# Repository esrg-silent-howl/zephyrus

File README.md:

# Zephyrus
## Hand Motion-Controlled Remote Car

### Problem Statement
Recent developments in research of motion-tracking and gesture-controlled robotic
products have shone a new light on entertainment, special needs teaching, and
accessibility-focused applications. Products like motion-sensing console controllers,
robotic arms, and prosthetics have popularized and extended the knowledge on gesture
and impulse-based technologies throughout the past few years, and their market
is predicted to continue to grow in the future.
To provide a better understanding of the concepts associated with the forementioned
technologies through Research and Development (R&D), the project will consist of a
gesture-controlled car with a wristband as a remote controller. The user will be able to
accelerate and steer the vehicle using natural wrist and finger movements.

Team:
- Hugo Carvalho @HugoDaniel99
- José Mendes @h0wl-14

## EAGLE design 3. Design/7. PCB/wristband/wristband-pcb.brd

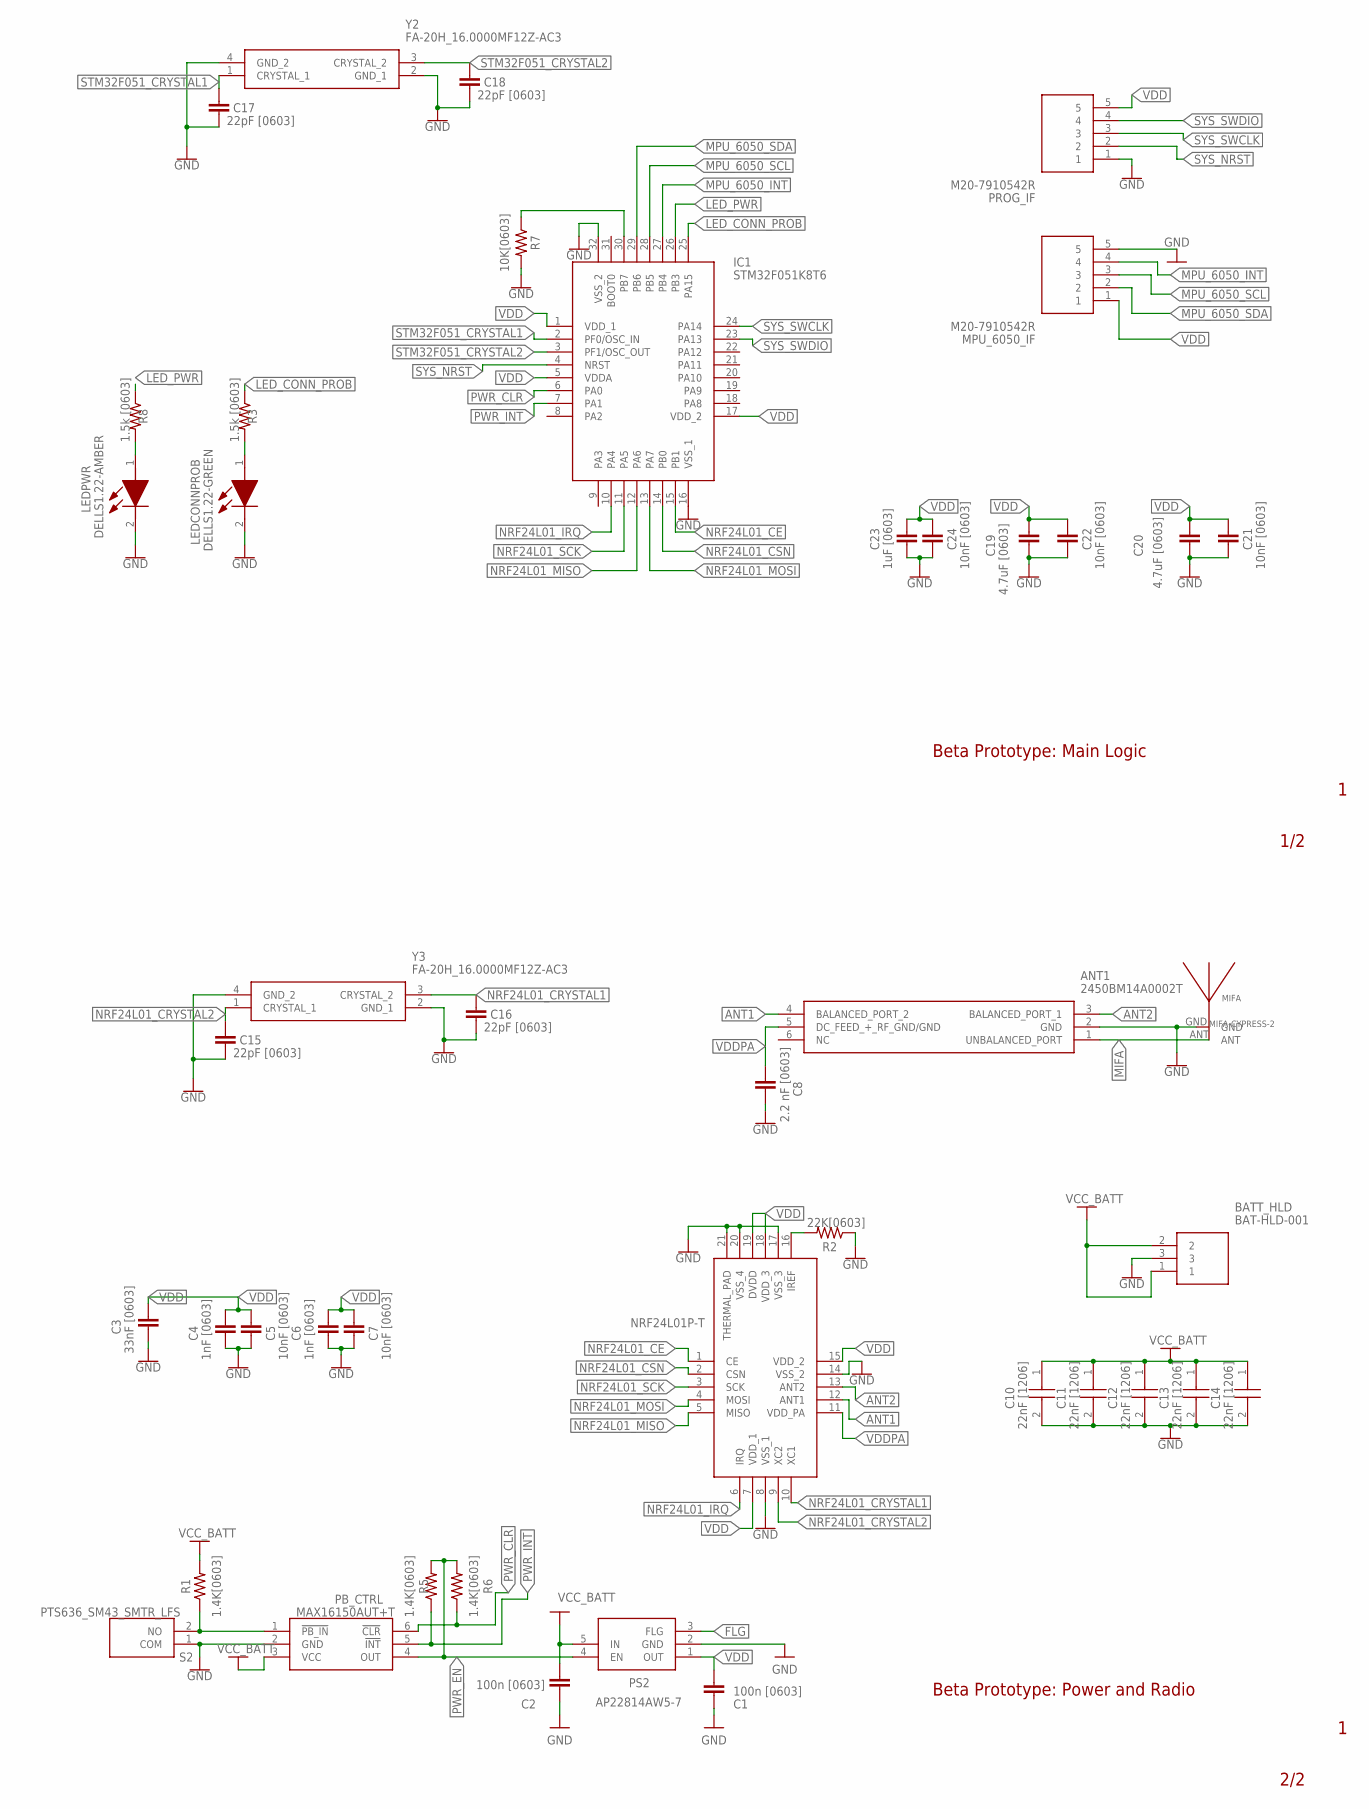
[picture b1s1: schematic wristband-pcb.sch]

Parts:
ANT1: 2450BM14A0002T
BATT_HLD: BAT-HLD-001; BATHLD001
C1, C2: 100n [0603]; CAPC1608X85
C3: 33nF [0603]; RESC0603_L
C4, C6: 1nF [0603]; RESC0603_L
C5, C7, C21, C22, C24: 10nF [0603]; RESC0603_L
C8: 2.2 nF [0603]; RESC0603_L
C10, C11, C12, C13, C14: 22nF [1206]; CAPC3216X180N
C15, C16, C17, C18: 22pF [0603]; RESC0603_L
C19, C20: 4.7uF [0603]; RESC0603_L
C23: 1uF [0603]; RESC0603_L
IC1: STM32F051K8T6; QFP80P900X900X160-32N
LEDCONNPROB: DELLS1.22-GREEN; KSDELLS122JHKI1
LEDPWR: DELLS1.22-AMBER; KSDELLS122JHKI1
MIFA: MIFA-CYPRESS-2
MPU_6050_IF: M20-7910542R; M207910542R
NRF24L01+: NRF24L01P-T; QFN50P400X400X95-21N
PB_CTRL: MAX16150AUT+T; SOT95P280X145-6N
PROG_IF: M20-7910542R; M207910542R
PS2: AP22814AW5-7; SOT95P285X130-5N
R1, R5, R6: 1.4K[0603]; RESC1608X60
R2: 22K[0603]; RESC1608X60
R3, R8: 1.5k [0603]; RESC1608X60
R7: 10K[0603]; RESC1608X60
S2: PTS636_SM43_SMTR_LFS; PTS636SM43SMTRLFS
Y2, Y3: FA-20H_16.0000MF12Z-AC3; FA20H160000MF12ZAC3

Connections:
ANT1: ANT1.4 (BALANCED_PORT_2), NRF24L01+.12 (ANT1)
ANT2: ANT1.3 (BALANCED_PORT_1), NRF24L01+.13 (ANT2)
FLG: PS2.3 (FLG)
GND: ANT1.2 (GND), BATT_HLD.3, C1.2, C2.2, C3.2, C4.2, C5.2, C6.2, C7.2, C8.2, C10.2, C11.2, C12.2, C13.2, C14.2, C15.2, C16.2, C17.2, C18.2, C19.2, C20.2, C21.2, C22.2, C23.2, C24.2, IC1.16 (VSS_1), IC1.32 (VSS_2), LEDCONNPROB.2 (K), LEDPWR.2 (K), MIFA.GND, MPU_6050_IF.5, NRF24L01+.8 (VSS_1), NRF24L01+.14 (VSS_2), NRF24L01+.17 (VSS_3), NRF24L01+.20 (VSS_4), NRF24L01+.21 (THERMAL_PAD), PB_CTRL.2 (GND), PROG_IF.1, PS2.2 (GND), R2.1, R7.2, S2.1 (COM), Y2.2 (GND_1), Y2.4 (GND_2), Y3.2 (GND_1), Y3.4 (GND_2)
LED_CONN_PROB: IC1.25 (PA15), R3.1
LED_PWR: IC1.26 (PB3), R8.1
MIFA: ANT1.1 (UNBALANCED_PORT), MIFA.ANT
MPU_6050_INT: IC1.27 (PB4), MPU_6050_IF.4
MPU_6050_SCL: IC1.28 (PB5), MPU_6050_IF.3
MPU_6050_SDA: IC1.29 (PB6), MPU_6050_IF.2
unnamed: PB_CTRL.1 (!PB_IN), R1.1, S2.2 (NO)
unnamed: NRF24L01+.16 (IREF), R2.2
unnamed: IC1.30 (PB7), R7.1
unnamed: LEDPWR.1 (A), R8.2
unnamed: LEDCONNPROB.1 (A), R3.2
NRF24L01_CE: IC1.15 (PB1), NRF24L01+.1 (CE)
NRF24L01_CRYSTAL1: C16.1, NRF24L01+.10 (XC1), Y3.3 (CRYSTAL_2)
NRF24L01_CRYSTAL2: C15.1, NRF24L01+.9 (XC2), Y3.1 (CRYSTAL_1)
NRF24L01_CSN: IC1.14 (PB0), NRF24L01+.2 (CSN)
NRF24L01_IRQ: IC1.10 (PA4), NRF24L01+.6 (IRQ)
NRF24L01_MISO: IC1.12 (PA6), NRF24L01+.5 (MISO)
NRF24L01_MOSI: IC1.13 (PA7), NRF24L01+.4 (MOSI)
NRF24L01_SCK: IC1.11 (PA5), NRF24L01+.3 (SCK)
PWR_CLR: IC1.6 (PA0), PB_CTRL.6 (!CLR), R6.1
PWR_EN: PB_CTRL.4 (OUT), PS2.4 (EN), R5.2, R6.2
PWR_INT: IC1.7 (PA1), PB_CTRL.5 (!INT), R5.1
STM32F051_CRYSTAL1: C17.1, IC1.2 (PF0/OSC_IN), Y2.1 (CRYSTAL_1)
STM32F051_CRYSTAL2: C18.1, IC1.3 (PF1/OSC_OUT), Y2.3 (CRYSTAL_2)
SYS_NRST: IC1.4 (NRST), PROG_IF.2
SYS_SWCLK: IC1.24 (PA14), PROG_IF.3
SYS_SWDIO: IC1.23 (PA13), PROG_IF.4
VCC_BATT: BATT_HLD.1, BATT_HLD.2, C2.1, C10.1, C11.1, C12.1, C13.1, C14.1, PB_CTRL.3 (VCC), PS2.5 (IN), R1.2
VDD: C1.1, C3.1, C4.1, C5.1, C6.1, C7.1, C19.1, C20.1, C21.1, C22.1, C23.1, C24.1, IC1.1 (VDD_1), IC1.5 (VDDA), IC1.17 (VDD_2), MPU_6050_IF.1, NRF24L01+.7 (VDD_1), NRF24L01+.15 (VDD_2), NRF24L01+.18 (VDD_3), NRF24L01+.19 (DVDD), PROG_IF.5, PS2.1 (OUT)
VDDPA: ANT1.5 (DC_FEED_+_RF_GND/GND), C8.1, NRF24L01+.11 (VDD_PA)

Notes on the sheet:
1/2
2/2
Beta Prototype: Main Logic
Beta Prototype: Power and Radio

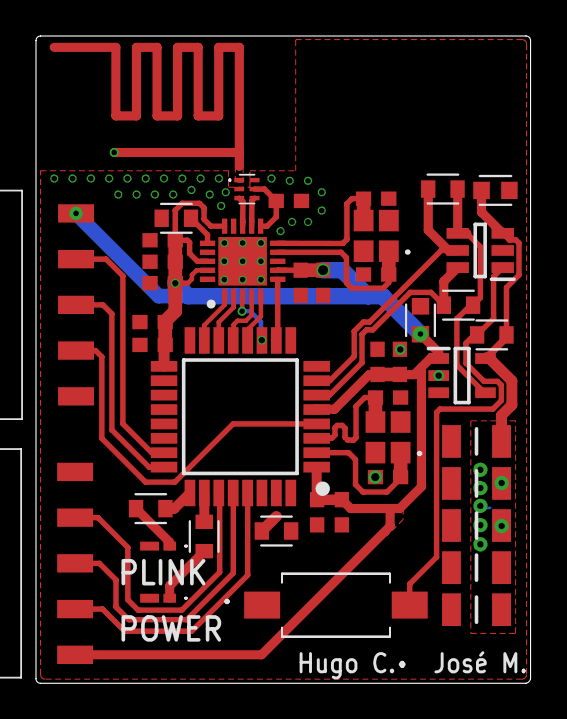
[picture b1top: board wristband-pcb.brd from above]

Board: 2 copper layers, 27.5 x 36.0 mm, 44 parts (1 on the bottom side), 33 nets.

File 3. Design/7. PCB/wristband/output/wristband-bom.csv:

Qty,Value,Device,Package,Parts,Description,Column1,_1
3,1.4K[0603],R-US_CHIP-0603(1608-METRIC),RESC1608X60,"R1, R5, R6",Resistor Fixed - ANSI,,
2,1.5k [0603],R-US_CHIP-0603(1608-METRIC),RESC1608X60,"R3, R8",Resistor Fixed - ANSI,,
2,100n [0603],C_CHIP-0603(1608-METRIC),CAPC1608X85,"C1, C2",Capacitor - Generic,,
1,10K[0603],R-US_CHIP-0603(1608-METRIC),RESC1608X60,R7,Resistor Fixed - ANSI,,
5,10nF [0603],CAPACITOR_0603_L,RESC0603_L,"C5, C7, C21, C22, C24",Generic chip capacitor,,
2,1nF [0603],CAPACITOR_0603_L,RESC0603_L,"C4, C6",Generic chip capacitor,,
1,1uF [0603],CAPACITOR_0603_L,RESC0603_L,C23,Generic chip capacitor,,
1,2.2 nF [0603],CAPACITOR_0603_L,RESC0603_L,C8,Generic chip capacitor,,
1,22K[0603],R-US_CHIP-0603(1608-METRIC),RESC1608X60,R2,Resistor Fixed - ANSI,,
5,22nF [1206],CL31B226KPHNNNE,CAPC3216X180N,"C10, C11, C12, C13, C14",22F +/-10% 10V Ceramic Capacitor X7R 1206 (3216 Metric),,
4,22pF [0603],CAPACITOR_0603_L,RESC0603_L,"C15, C16, C17, C18",Generic chip capacitor,,
1,2450BM14A0002T,2450BM14A0002T,2450BM14A0002T,ANT1,"JOHANSON TECHNOLOGY - 2450BM14A0002T - BALUN, 2.45GHZ, IMPEDANCE MATCHED",,
1,33nF [0603],CAPACITOR_0603_L,RESC0603_L,C3,Generic chip capacitor,,
2,4.7uF [0603],CAPACITOR_0603_L,RESC0603_L,"C19, C20",Generic chip capacitor,,
1,AP22814AW5-7,AP22814AW5-7,SOT95P285X130-5N,PS2,"DiodesZetex AP22814AW5-7, USB Power Switch, High Side, 65m, 1.6 V min. 5-Pin, SOT25",,
1,BAT-HLD-001,BAT-HLD-001,BATHLD001,BATT_HLD,Coin Cell Battery Holders Linx CR2032 Battery Holder,,
1,DELLS1.22-AMBER,KS_DELLS1.22-JHKI-1,KSDELLS122JHKI1,LEDPWR,Standard LEDs - SMD Super Red TOPLED E 1608,,
1,DELLS1.22-GREEN,KS_DELLS1.22-JHKI-1,KSDELLS122JHKI1,LEDCONNPROB,Standard LEDs - SMD Super Red TOPLED E 1608,,
2,FA-20H_16.0000MF12Z-AC3,FA-20H_16.0000MF12Z-AC3,FA20H160000MF12ZAC3,"Y2, Y3",Crystals 16MHz 10ppm 9pF -20C +75C,,
2,M20-7910542R,M20-7910542R,M207910542R,"MPU_6050_IF, PROG_IF",Headers & Wire Housings 5 WAY SIL HORIZ SMT SKT T&R,,
1,MAX16150AUT+T,MAX16150AUT+T,SOT95P280X145-6N,PB_CTRL,Supervisory Circuits Nano-Power Pushbutton ON/OFF Controller with 15kV ESD Protection and Programmable Timer,,
1,MIFA-CYPRESS-2,MIFA-CYPRESS-2,MIFA-CYPRESS-2,MIFA,,,
1,NRF24L01P-T,NRF24L01P-T,QFN50P400X400X95-21N,NRF24L01+,"RF Transceiver IC 2.4GHz ISM Band QFN20 Nordic Semiconductor NRF24L01P-T, RF Transceiver 2400MHz to 2483.5MHz 1.9  3.6 V 20-Pin QFN",,
1,PTS636_SM43_SMTR_LFS,PTS636_SM43_SMTR_LFS,PTS636SM43SMTRLFS,S2,"Tactile Switches Tact 50mA 12VDC, 6.0x3.5, 4.3mm H, 180gf, G leads, No ground pin, Black Actuator",,
1,STM32F051K8T6,STM32F051K8T6,QFP80P900X900X160-32N,IC1,Source:  Datasheet,,

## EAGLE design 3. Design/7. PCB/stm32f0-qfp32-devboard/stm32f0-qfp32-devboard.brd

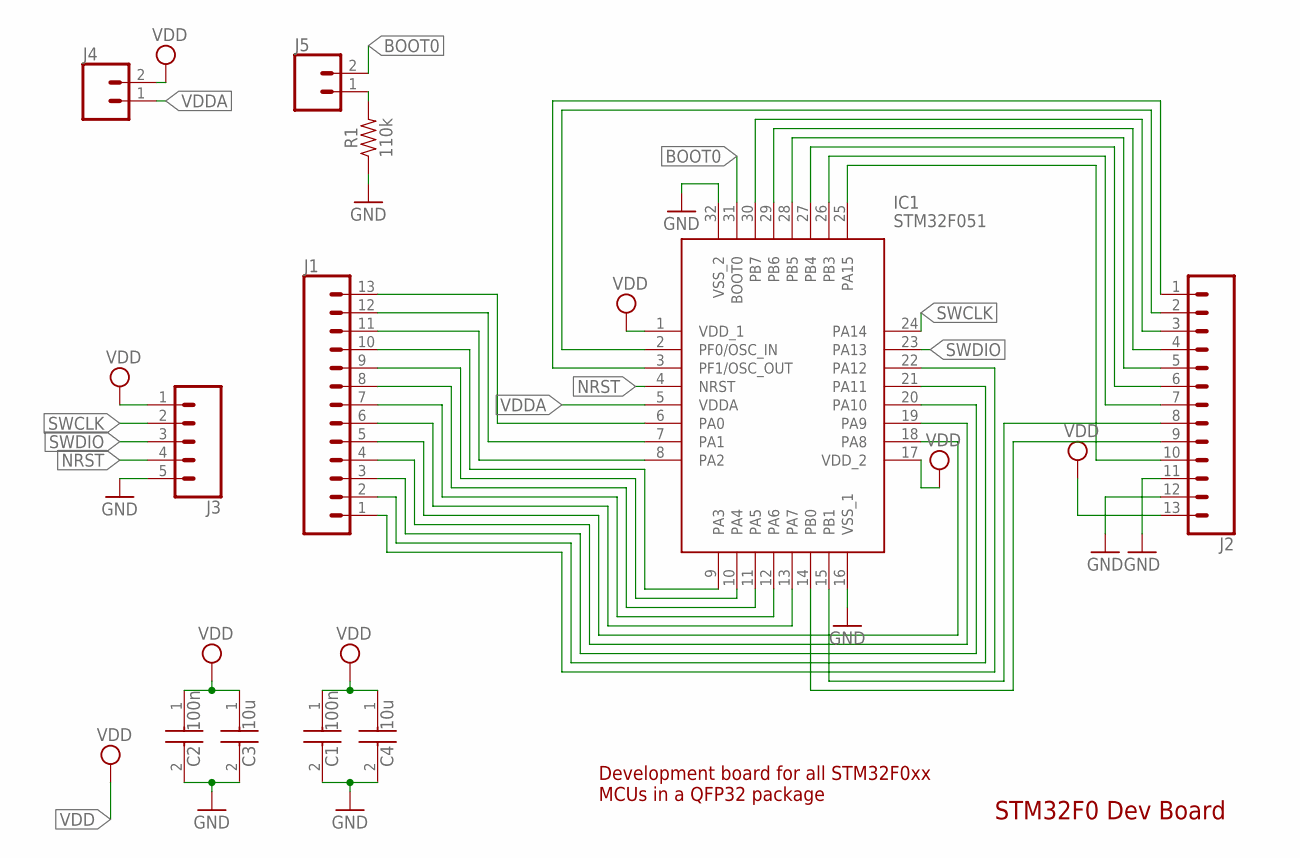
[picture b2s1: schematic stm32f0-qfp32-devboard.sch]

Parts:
C1, C2: 100n; CAPC2012X100N
C3, C4: 10u; CAPC3216X180N
IC1: STM32F051; QFP80P900X900X160-32N
J1, J2: CONN_13; 1X13
J3: CONN_05; 1X05
J4, J5: CONN_02; 1X02
R1: 110k; 0805

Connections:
BOOT0: IC1.31 (BOOT0), J5.2
GND: C1.2, C2.2, C3.2, C4.2, IC1.16 (VSS_1), IC1.32 (VSS_2), J2.11, J2.12, J3.5, R1.1
unnamed: IC1.6 (PA0), J1.13
unnamed: IC1.7 (PA1), J1.12
unnamed: IC1.2 (PF0/OSC_IN), J2.2
unnamed: IC1.3 (PF1/OSC_OUT), J2.1
unnamed: IC1.30 (PB7), J2.3
unnamed: IC1.29 (PB6), J2.4
unnamed: IC1.28 (PB5), J2.5
unnamed: IC1.27 (PB4), J2.6
unnamed: IC1.26 (PB3), J2.7
unnamed: IC1.15 (PB1), J2.8
unnamed: IC1.14 (PB0), J2.9
unnamed: IC1.8 (PA2), J1.11
unnamed: IC1.9 (PA3), J1.10
unnamed: IC1.10 (PA4), J1.9
unnamed: IC1.11 (PA5), J1.8
unnamed: IC1.12 (PA6), J1.7
unnamed: IC1.13 (PA7), J1.6
unnamed: IC1.18 (PA8), J1.5
unnamed: IC1.19 (PA9), J1.4
unnamed: IC1.20 (PA10), J1.3
unnamed: IC1.21 (PA11), J1.2
unnamed: IC1.22 (PA12), J1.1
unnamed: IC1.25 (PA15), J2.10
unnamed: J5.1, R1.2
NRST: IC1.4 (NRST), J3.4
SWCLK: IC1.24 (PA14), J3.2
SWDIO: IC1.23 (PA13), J3.3
VDD: C1.1, C2.1, C3.1, C4.1, IC1.1 (VDD_1), IC1.17 (VDD_2), J2.13, J3.1, J4.2
VDDA: IC1.5 (VDDA), J4.1

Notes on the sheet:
STM32F0 Dev Board
Development board for all STM32F0xx MCUs in a QFP32 package

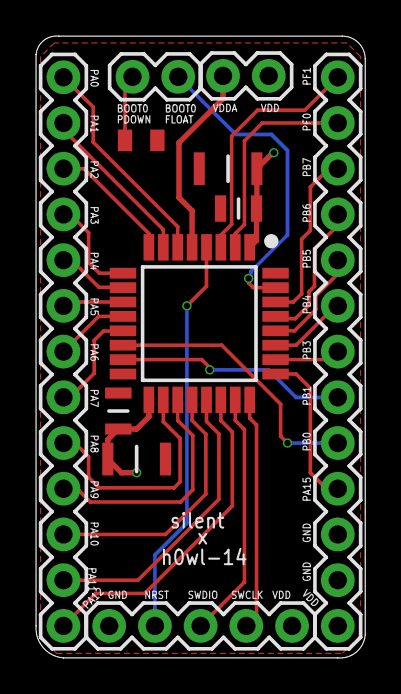
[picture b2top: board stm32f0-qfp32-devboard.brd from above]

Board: 2 copper layers, 18.3 x 34.6 mm, 11 parts (0 on the bottom side), 31 nets.

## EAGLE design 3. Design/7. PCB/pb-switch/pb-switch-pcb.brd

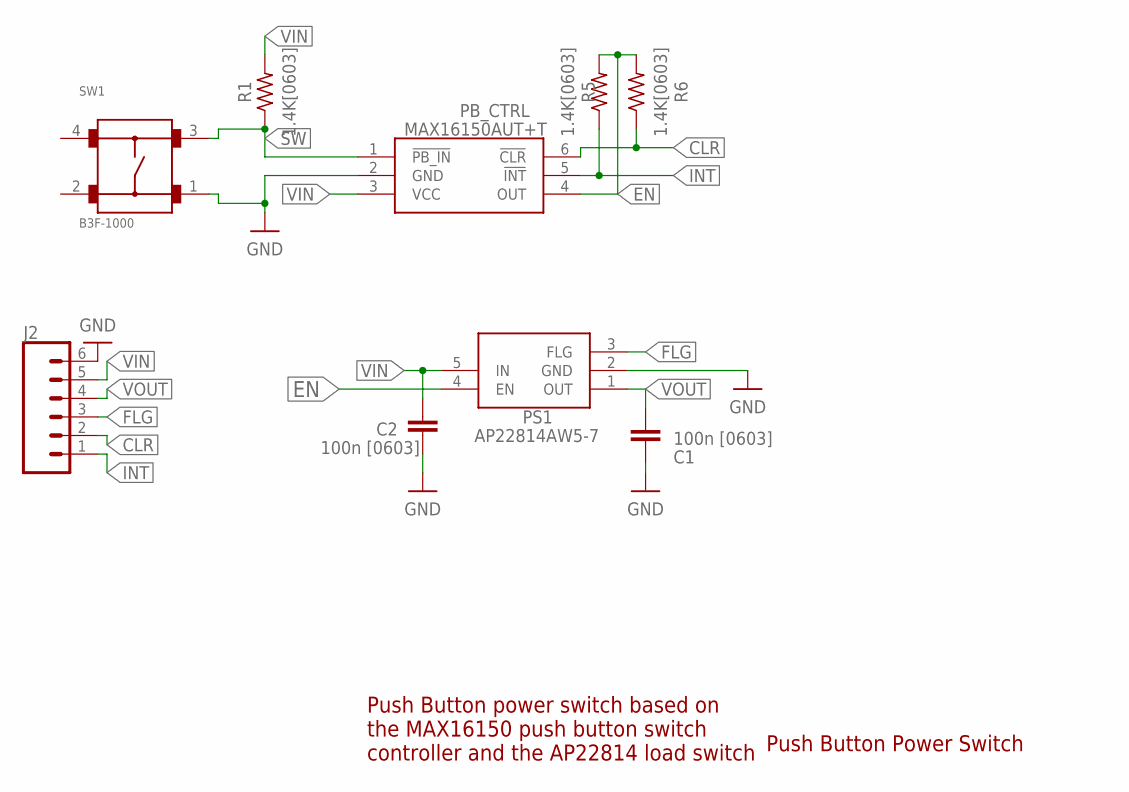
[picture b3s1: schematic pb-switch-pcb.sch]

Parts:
C1, C2: 100n [0603]; CAPC1608X85
J2: CONN_06SILK_FEMALE_PTH; 1X06
PB_CTRL: MAX16150AUT+T; SOT95P280X145-6N
PS1: AP22814AW5-7; SOT95P285X130-5N
R1, R5, R6: 1.4K[0603]; RESC1608X60
SW1: B3F-1000

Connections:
CLR: J2.2, PB_CTRL.6 (!CLR), R6.1
EN: PB_CTRL.4 (OUT), PS1.4 (EN), R5.2, R6.2
FLG: J2.3, PS1.3 (FLG)
GND: C1.2, C2.2, J2.6, PB_CTRL.2 (GND), PS1.2 (GND), SW1.1
INT: J2.1, PB_CTRL.5 (!INT), R5.1
SW: PB_CTRL.1 (!PB_IN), R1.1, SW1.3
VIN: C2.1, J2.5, PB_CTRL.3 (VCC), PS1.5 (IN), R1.2
VOUT: C1.1, J2.4, PS1.1 (OUT)

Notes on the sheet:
Push Button Power Switch
Push Button power switch based on the MAX16150 push button switch controller and the AP22814 load switch

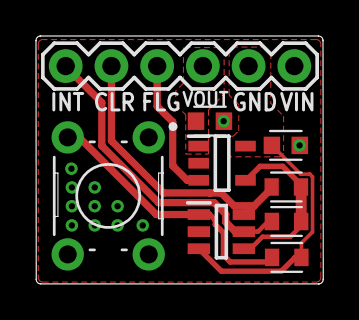
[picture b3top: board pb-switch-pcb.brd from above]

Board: 2 copper layers, 16.0 x 13.8 mm, 9 parts (0 on the bottom side), 8 nets.

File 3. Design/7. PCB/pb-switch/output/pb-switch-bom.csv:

Exported,,,,,,,
Qty,Value,Device,Package,Parts,Description,Column1,_1
1,,CONN_06SILK_FEMALE_PTH,1X06,J2,Multi connection point. Often used as Generic Header-pin footprint for 0.1 inch spaced/style header connections,,
3,1.4K[0603],R-US_CHIP-0603(1608-METRIC),RESC1608X60,"R1, R5, R6",Resistor Fixed - ANSI,,
2,100n [0603],C_CHIP-0603(1608-METRIC),CAPC1608X85,"C1, C2",Capacitor - Generic,,
1,AP22814AW5-7,AP22814AW5-7,SOT95P285X130-5N,PS1,"DiodesZetex AP22814AW5-7, USB Power Switch, High Side, 65m, 1.6 V min. 5-Pin, SOT25",,
1,B3F-1000,B3F-1000,B3F-1000,SW1,Tactile Switch SPST-NO Top Actuated Through Hole,,
1,MAX16150AUT+T,MAX16150AUT+T,SOT95P280X145-6N,PB_CTRL,Supervisory Circuits Nano-Power Pushbutton ON/OFF Controller with 15kV ESD Protection and Programmable Timer,,
,,,,,,,
,,,,,,,
Final,,,,,,,
Qty,Value,Device,Package,Parts,Description,Column1,_1
3,1.4 KOhm,Resistor,RES0603,"R1, R5, R6",Resistor Fixed - ANSI,,
2,100 nF,Capacitor,CAP0603,"C1, C2",Capacitor - Generic,,
1,-,AP22814AW5-7,SOT23-5,PS1,High Side Power Switch,,
1,-,B3F-1000,B3F-1000,SW1,Tactile Switch SPST-NO Top Actuated Through Hole,,
1,-,MAX16150AUT+T,SOT23-6,PB_CTRL,Pushbutton ON/OFF Controller,,

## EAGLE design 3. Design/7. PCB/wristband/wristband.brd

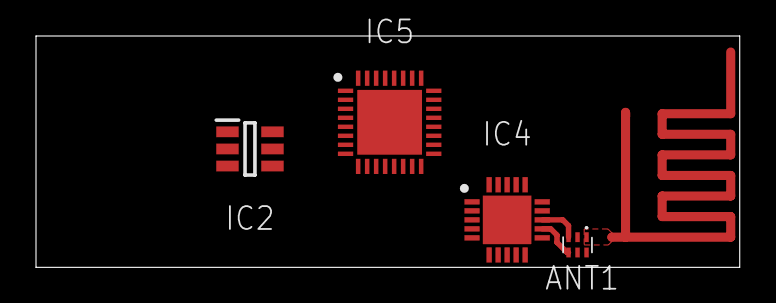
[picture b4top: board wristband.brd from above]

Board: 2 copper layers, 39.1 x 12.9 mm, 5 parts (0 on the bottom side), 4 nets.

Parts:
ANT1: 2450BM14A0002T
IC2: MAX16150AUT+T; SOT95P280X145-6N
IC4: NRF24L01P-T; QFN50P400X400X95-21N
IC5: STM32F051K6U6; QFN50P500X500X60-33N
U$2: MIFA-CYPRESS-2

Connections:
ANT1: ANT1.4, IC4.12
ANT2: ANT1.3, IC4.13
GND: ANT1.2, U$2.GND
unnamed: ANT1.1, U$2.ANT

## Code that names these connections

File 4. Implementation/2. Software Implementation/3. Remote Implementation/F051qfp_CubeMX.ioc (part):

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Mcu.Name=STM32F051K6Tx
Mcu.Package=LQFP32
Mcu.UserName=STM32F051K6Tx
PA0.GPIOParameters=GPIO_Speed,PinState,GPIO_PuPd,GPIO_Label
PA0.GPIO_Label=PWR_CLR
PA0.GPIO_PuPd=GPIO_NOPULL
PA0.GPIO_Speed=GPIO_SPEED_FREQ_MEDIUM
PA0.PinState=GPIO_PIN_SET
PA0.Signal=GPIO_Output
PA1.GPIOParameters=GPIO_PuPd,GPIO_Label,GPIO_ModeDefaultEXTI
PA1.GPIO_Label=PWR_INT
PA1.GPIO_ModeDefaultEXTI=GPIO_MODE_IT_FALLING
PA1.GPIO_PuPd=GPIO_PULLUP
PA1.Signal=GPXTI1
PA10.GPIOParameters=GPIO_Speed,GPIO_Label
PA10.GPIO_Label=LED_DEBUG
PA10.GPIO_Speed=GPIO_SPEED_FREQ_HIGH
PA10.Signal=GPIO_Output
PA13.Mode=Serial_Wire
PA13.Signal=SYS_SWDIO
PA14.Mode=Serial_Wire
PA14.Signal=SYS_SWCLK
PA15.GPIOParameters=GPIO_Label
PA15.GPIO_Label=LED_CONN_PROB
PA15.Signal=GPIO_Output
PA4.GPIOParameters=GPIO_PuPd,GPIO_Label,GPIO_ModeDefaultEXTI
PA4.GPIO_Label=NRF24L01_IRQ
PA4.GPIO_ModeDefaultEXTI=GPIO_MODE_IT_FALLING
PA4.GPIO_PuPd=GPIO_PULLUP
PA4.Signal=GPXTI4
PA5.GPIOParameters=GPIO_Label
PA5.GPIO_Label=NRF24L01_SCK
PA5.Mode=Full_Duplex_Master
PA5.Signal=SPI1_SCK
PA6.GPIOParameters=GPIO_Label
PA6.GPIO_Label=NRF24L01_MISO
PA6.Mode=Full_Duplex_Master
PA6.Signal=SPI1_MISO
PA7.GPIOParameters=GPIO_Label
PA7.GPIO_Label=NRF24L01_MOSI
PA7.Mode=Full_Duplex_Master
PA7.Signal=SPI1_MOSI
PA9.GPIOParameters=GPIO_Speed,PinState,GPIO_Label
PA9.GPIO_Label=FLAG_DEBUG
PA9.GPIO_Speed=GPIO_SPEED_FREQ_HIGH
PA9.PinState=GPIO_PIN_RESET
PA9.Signal=GPIO_Output
PB0.GPIOParameters=PinState,GPIO_PuPd,GPIO_Label
PB0.GPIO_Label=NRF24L01_CSN
PB0.GPIO_PuPd=GPIO_PULLUP
PB0.PinState=GPIO_PIN_SET
PB0.Signal=GPIO_Output
PB1.GPIOParameters=GPIO_PuPd,GPIO_Label
PB1.GPIO_Label=NRF24L01_CE
PB1.GPIO_PuPd=GPIO_PULLUP
PB1.Signal=GPIO_Output
PB3.GPIOParameters=GPIO_PuPd,GPIO_Label
PB3.GPIO_Label=LED_PWR
PB3.GPIO_PuPd=GPIO_NOPULL
PB3.Signal=S_TIM2_CH2
PB4.GPIOParameters=GPIO_Label
PB4.GPIO_Label=MPU_6050_SDA_BRIDGE
PB4.Signal=GPIO_Analog
PB5.GPIOParameters=GPIO_PuPd,GPIO_Label,GPIO_ModeDefaultEXTI
PB5.GPIO_Label=MPU_6050_INT
PB5.GPIO_ModeDefaultEXTI=GPIO_MODE_IT_FALLING
PB5.GPIO_PuPd=GPIO_PULLUP
PB5.Signal=GPXTI5
PB6.GPIOParameters=GPIO_Label
PB6.GPIO_Label=MPU_6050_SCL
PB6.Mode=I2C
PB6.Signal=I2C1_SCL
PB7.GPIOParameters=GPIO_Label
PB7.GPIO_Label=MPU_6050_SDA
PB7.Mode=I2C
PB7.Signal=I2C1_SDA
PF0-OSC_IN.GPIOParameters=GPIO_Label
PF0-OSC_IN.GPIO_Label=STM32F051_CRYSTAL1
PF0-OSC_IN.Mode=HSE-External-Oscillator
PF0-OSC_IN.Signal=RCC_OSC_IN
PF1-OSC_OUT.GPIOParameters=GPIO_Label
PF1-OSC_OUT.GPIO_Label=STM32F051_CRYSTAL2
PF1-OSC_OUT.Mode=HSE-External-Oscillator
PF1-OSC_OUT.Signal=RCC_OSC_OUT
RCC.HSE_VALUE=16000000
RCC.SYSCLKFreq_VALUE=48000000
RCC.SYSCLKSource=RCC_SYSCLKSOURCE_PLLCLK
board=custom

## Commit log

2020-10-20 ADD: Project Plan
2020-10-20 ADD: First commit
2020-10-20 ADD: Planned project structure
2020-10-20 RM: Diverging from the original repository
2020-10-21 ADD: Problem Statement
2020-10-23 ADD: System Overview
2020-10-23 ADD: Problem Statement Analysis diagram
2020-10-23 UPTD: Fixed small inconsistency in the System Overview Diagram
2020-10-23 UPTD: Simplified and generalized the wireless connection blocks in the System Overview diragram
2020-10-23 ADD: Software Architecture
2020-10-23 UPDT: Software Architecture visual tweaks
2020-10-26 ADD: Hardware Architecture
2020-10-26 UPDT: Hardware Architecture diagram tweaks
2020-10-27 UPDT: Small functional changes to the schematics
2020-10-27 ADD: Gantt Diagram
2020-10-27 ADD: Delivered version of the Project Pan
2020-10-27 ADD|UPDT: Separated the Software Architecture into Local and Remote
2020-10-27 ADD: Sensor frameworks added to the local system's Software Overview
2020-10-29 ADD: Remote and Local Overview
2020-10-29 FIX: System Overview file opening problem
2020-10-29 ADD: Local Events
2020-10-30 ADD: Market Study images
2020-10-30 FIX: HW Architecture Tensorflow + ADD: Model Conversion
2020-10-30 UPDT: Analysys Diagram tweaks
2020-10-30 ADD: Local events table
2020-10-31 FIX: Functional corrections to the Local Events table
2020-10-31 ADD: Local - RL folder
2020-10-31 ADD: Use Case Diagrams
2020-11-01 UPDT: Aesthetic changes to use case diagrams
2020-11-01 First version of the Sequence Diagrams
2020-11-02 UPDT: Finished Sequence Diagrams
2020-11-02 FIX: Corrections made to the Use Case diagrams
2020-11-02 FIX: Remote Sequence Diagram
2020-11-02 ADD: Market Images to problem statement
2020-11-03 ADD: Deliverables section and Shopping List
2020-11-04 ADD: Initial Budget Table
2020-11-04 UPDT: HW Architecture Diagram minor changes
2020-11-04 UPDT: Some more HW diagram changes
2020-11-04 ADD: State Machine Diagram - Remote
2020-11-04 ADD/UPDT: Material acquisition documentation
2020-11-05 UPDT: Local Events Table
2020-11-05 UPDT: Use Case Diagram Tweaks
2020-11-05 ADD/UPDT: Added Local and Updated Remote State Machine Diagrams
2020-11-06 FIX: Use Case Diagrams
2020-11-06 ADD/UPDT: Updated shopping list with the last purchase
2020-11-06 FIX: Solved functional problems related to the RL model in the tables and diagrams
2020-11-06 FIX: Fixed arrows in the System Overview Diagram
2020-11-11 FIX: Use case diagram local - added arrow
2020-11-16 FIX: Small improvements in the Local System's State Machine Diagram
2020-11-16 FIx: Image tweaks for PowerPoint
2020-11-16 ADD: Analysis Files: ppt, pdf, tex
2020-11-16 FIX: Fixed some problems in the analysis files: pdf, tex
2020-11-18 FIX|ADD: Fixed the problem pointed to by Professor in presentation and added the screenplay
2020-11-21 ADD: STM32F051 dev board schematic and PCB
2020-11-21 ADD: STM32F051 dev board schematic and pcb snapshots
2020-11-22 ADD: Waterfall Diagram
2020-11-22 ADD: Gyroscope & Accelerometer Flowchart + Odel conversion diagram tweak
2020-11-22 ADD: Gyroscope & Accelerometer Flowchart + Model conv. diagram tweaks
2020-11-22 UPDT: Finished gyroscope module's flowchart
2020-11-22 ADD: MPU-6050 interrupt table
2020-11-22 ADD: Images, CAD models and datasheets relative to the Hardware Overview
2020-11-23 ADD: STM32F051 dev board PCB list entry and invoice
2020-11-23 FIX: Corrections to the Gyroscope flowchart in the Software Specifications
2020-11-23 ADD: LM2596 module image (Hardware Specification)
2020-11-23 ADD: Task Timeline
2020-11-23 UPDT: Minor Teaks - Task Timeline
2020-11-23 ADD: RF Flowchart
2020-11-23 ADD: Task Priority Diagram
2020-11-24 UPDT: Visual Tweaks to the flowcharts and timeline
2020-11-24 FIX: HW Achitecture M0+ -> M0
2020-11-27 ADD: Hardware Specification
2020-11-27 ADD: SPI protocol images
2020-11-27 ADD: STM32F0 dev board 3D model
2020-11-29 ADD: Boilerplate material for the wristband PCB
2020-11-29 ADD: I2C schematics
2020-12-03 UPDT: Waterfall schematic to PDF
2020-12-03 ADD: RL Flowchart
2020-12-05 ADD: Neural Network Initial Design
2020-12-05 ADD: First Implementation files and non-working nRF24L01 test version
2020-12-05 FIX|UPDT: Small fixes and pdf exports in some analysis diagrams
2020-12-05 ADD: Power supply overview pdf export
2020-12-05 ADD: Peripheral interface media and diagrams
2020-12-05 ADD|UPDT: Added new antenna library files and initial nRF24L01-balun/filter-antenna interaction sketch
2020-12-05 ADD: acc and gyro task local
2020-12-05 ADD: acc and gyro task remote
2020-12-05 ADD: created drawios for uss and motor flowcharts
2020-12-05 UPDT: RL Flowchart
2020-12-05 UPDT: Task priority level
2020-12-05 UPDT: RF management thread flowchart
2020-12-05 FIX: Fixed STM32F0 devboard dimensions schematic
2020-12-05 UPDT: General flowchart and export update
2020-12-06 UPDT: Task priotity level diagram for both systems finished
2020-12-06 FIX: minor fix - acc and gyro flowchart
2020-12-06 ADD: Task communication schematic
2020-12-06 ADD|UPDT|FIX: Added last task flowcharts, deleted/corrected unnecessary ones and corrected exports
2020-12-06 FIX: Task Communications - daugther isr mistake
2020-12-07 ADD: System test cases
2020-12-08 ADD: STM32F051 interface
2020-12-08 FIX: Hardware architecture diagram export
2020-12-08 ADD|UPDT|FIX: Corrected Dev Board exports and finished wristband board's schematic
2020-12-08 Added first version of the powerpoint presentation
2020-12-10 ADD|UPDT: Finished presentation
2020-12-14 UPDT: Added all work done on the Wristband PCB board so far
2020-12-14 ADD: PB switch PCB
2020-12-14 ADD|UPDT: PB switch PCB 3D model
2020-12-15 ADD: MPU6050 and Motor Driver Test Projects
2020-12-18 UPDT: PCB Wristband
2020-12-18 ADD|UPDT: FreeRTOS Testing, remote and local implementation boilerplate code
2020-12-18 ADD: .gitignore to both implementation directories
2020-12-18 FIX: replaced load switching MOSFET with an actual load switch
2020-12-19 UPDT: Added bypass capacitor at the output, enlarged power paths and optimized power
2020-12-19 ADD: Working ultrasonic sensor test module
2020-12-19 UPDT: MPU6050 Interrupt Tests
2020-12-19 UPDT: Added Load Switch to Wristband PCB
2020-12-19 ADD: Convention guidelines file
2020-12-20 UPDT: Updated wristband PCB design with new connections and slightly different layout
2020-12-20 UPDT: Thermal improvements to the pushbutton switch PCB
2020-12-20 UPDT: Wristband PCB
2020-12-20 UPDT: Further updates to the wristband PCB
2020-12-20 UPDT: Functional part of the wristband PCB done
2020-12-20 UPDT: Signature overlay added to wristband PCB
2020-12-20 UPDT: Almost all 3D models applied in the wristband pcb
2020-12-21 ADD|UPDT: Exported new and corrected old 3D models, 2D models and technical drawings of all PCBs
2020-12-21 ADD: pb-switch and stm32f0-qfp32-devboard BOM
2020-12-22 ADD: pb-switch and wristband CAM files
2020-12-22 UPDT: Shopping documents
2020-12-22 FIX: Local Unit Tests Table (Minor Changes)
2020-12-22 ADD: First task-related code
2020-12-22 UPDT: Project's Readme changes
2020-12-22 ADD: _zTasks.h, _zTasks.c, _attr.h
2020-12-23 UPDT: added functionality to rtos wrapper and created practical test setup for semaphores and notifications
2020-12-23 UPDT: Working test setup for semaphores and notifications
2020-12-23 UPDT: Local Implementation - start thread sleep and battery level
2020-12-23 UPDT: Battery level assessment dynamic added
2020-12-23 ADD: Run Mode vs Low Power Modes Simulations
2020-12-23 ADD: Missing simulation picture (peripheral consumption))
2020-12-23 ADD: Power Simulations PDFs
2020-12-24 UPDT: Battery level assessment dynamic done and tested
2020-12-24 UPDT: Sleep mode added to the main thread
2020-12-26 UPDT: Ported working ultrasonic sensor module from the testing setup to the local system's implementation
2020-12-27 UPDT: USS module working off timers
2020-12-27 ADD|UPDT: Added non-tested IMU module and updated thread code and rtos wrapper to use wrapper queueing functions
2020-12-27 ADD: Motor speed control
2020-12-27 UPDT: Conventions and deployment documents
2020-12-27 UPDT: Added working IMU module and task
2020-12-28 UPDT: A few updates to the local implementation concerning timing
2020-12-28 UPDT: Threads Synchronization changes
2020-12-28 ADD: Remote Timeline V2
2020-12-28 ADD|UPDT: Exported task timelines
2020-12-28 UPDT: Timing implementation done and tested
2020-12-28 RM|UPDT: General cleanup
2020-12-28 ADD: High-quality rendering of the stm32f0 devboard
2020-12-28 UPDT: Small update to the testing module
2020-12-30 UPDT: Low Battery check routine working on remote system working
2020-12-30 UPDT: Working sleep task in remote implementation
2020-12-30 UPDT: Working IMU module
2020-12-31 UPDT: Working shutdown request response
2020-12-31 UPDT: Working shutdown request response on remote
2020-12-31 ADD|UPDT : Further tests on NRF24L01+
2020-12-31 FIX: More reliable startup in debug mode
2020-12-31 UPDT: TIM3 doing power LED and ADC timing
2020-12-31 UPDT: Added low power mode to MPU module
2021-01-02 ADD: Tijen Majerle's nrf24l01 modules
2021-01-02 ADD: Working transmitter (F051) and receiver (F767) modules under testing
2021-01-02 ADD: Low power design img
2021-01-02 UPDT: Small functional improvements and optimizations to remote
2021-01-02 ADD: Preliminary power consumption simulations for the remote system
2021-01-02 ADD: ADC calibration sequence to remote
2021-01-02 UPDT: Remote task timeline to include only 1 sampling instance and interrupts
2021-01-03 UPDT: Working RF module in remote systems's implementation
2021-01-05 ADD: Zephyrus' RL Python Notebook + TFLite model
2021-01-06 ADD: Local and Remote Task Timelines w/ IdleTask
2021-01-06 ADD: RL Deployment test
2021-01-06 ADD: Local Timeline Events Table
2021-01-06 ADD|UPDT: Remote Task Timeline Event Table + Remote task timeline fix
2021-01-06 UPDT: RL Test additions
2021-01-06 ADD: Idle Hook to Local System
2021-01-07 UPDT: Working handshake in remote implementation and local testing
2021-01-07 UPDT: Handshake working
2021-01-07 UPDT: Patch to the handshake
2021-01-07 UPDT: Synchronization apparently not working
2021-01-09 UPDT: Remote working with new pinout
2021-01-10 ADD: New exports for the report
2021-01-11 Project at the time of delivery

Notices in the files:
parts and their libraries:
SparkFun-Connectors: Licensing: Creative Commons ShareAlike 4.0 International - https://creativecommons.org/licenses/by-sa/4.0
mpad_v2.1: License : GNU General Public License version 2 (see bottom)
SparkFun-Aesthetics: Released under the Creative Commons Attribution Share-Alike 4.0 License
